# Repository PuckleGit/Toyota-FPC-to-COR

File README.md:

# Toyota Fuel Pump Control to Circuit Opening Relay
Remake of circuit schematics and diagrams of the Fuel Pump Control module to Circuit Opening Relay originally created by wilbo666 for use on the Toyota Supra/Soarer based vehicles

Original wiring and information about the control and methodoloy can be found here http://wilbo666.pbworks.com/w/page/43601575/Toyota%20FPC%20to%20COR%20Wiring

Schematics have been built using KiCAD 9.0 adding specifc component specifcations into the schematics for clairity and ease of use. 

The design also incorparates the use of a relay interface to fit an ISO Micro relay

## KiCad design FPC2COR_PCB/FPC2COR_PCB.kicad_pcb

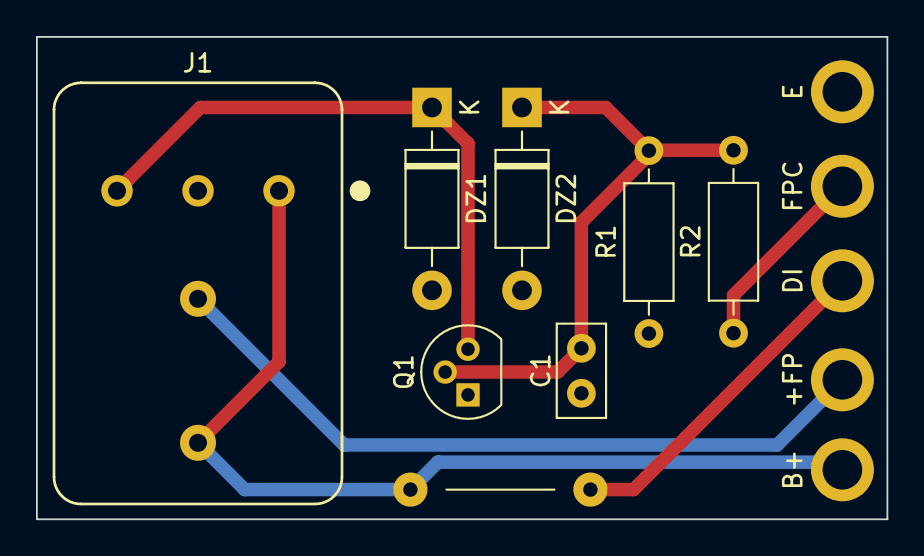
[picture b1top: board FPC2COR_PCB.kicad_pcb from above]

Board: 2 copper layers, 47.2 x 26.8 mm, 13 parts (0 on the bottom side), 7 nets.

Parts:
+FP: MountingHole_2.2mm_M2_ISO7380_Pad
B+: MountingHole_2.2mm_M2_ISO7380_Pad
C1: 1uF_0603_25V; C_Disc_D5.0mm_W2.5mm_P2.50mm
DI: MountingHole_2.2mm_M2_ISO7380_Pad
DZ1, DZ2: 1N4746A; D_DO-41_SOD81_P10.16mm_Horizontal
E: MountingHole_2.2mm_M2_ISO7380_Pad
FPC: MountingHole_2.2mm_M2_ISO7380_Pad
J1: V23333-Z0002-B049
JP1: JUP_P10mm
Q1: 2N7000; TO-92
R1: 1M; R_Axial_DIN0207_L6.3mm_D2.5mm_P10.16mm_Horizontal
R2: 1k; R_Axial_DIN0207_L6.3mm_D2.5mm_P10.16mm_Horizontal

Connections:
+B: B+.1, J1.1 (COIL+), J1.3 (COM), JP1.1
+FP: +FP.1, J1.5 (NO)
DI: DI.1, JP1.2
E: C1.2, DZ1.2 (A), DZ2.2 (A), E.1, Q1.1 (S), R1.1
FPC: FPC.1, R2.1
unnamed: DZ1.1 (K), J1.2 (COIL-), Q1.3 (D)
unnamed: C1.1, DZ2.1 (K), Q1.2 (G), R1.2, R2.2
